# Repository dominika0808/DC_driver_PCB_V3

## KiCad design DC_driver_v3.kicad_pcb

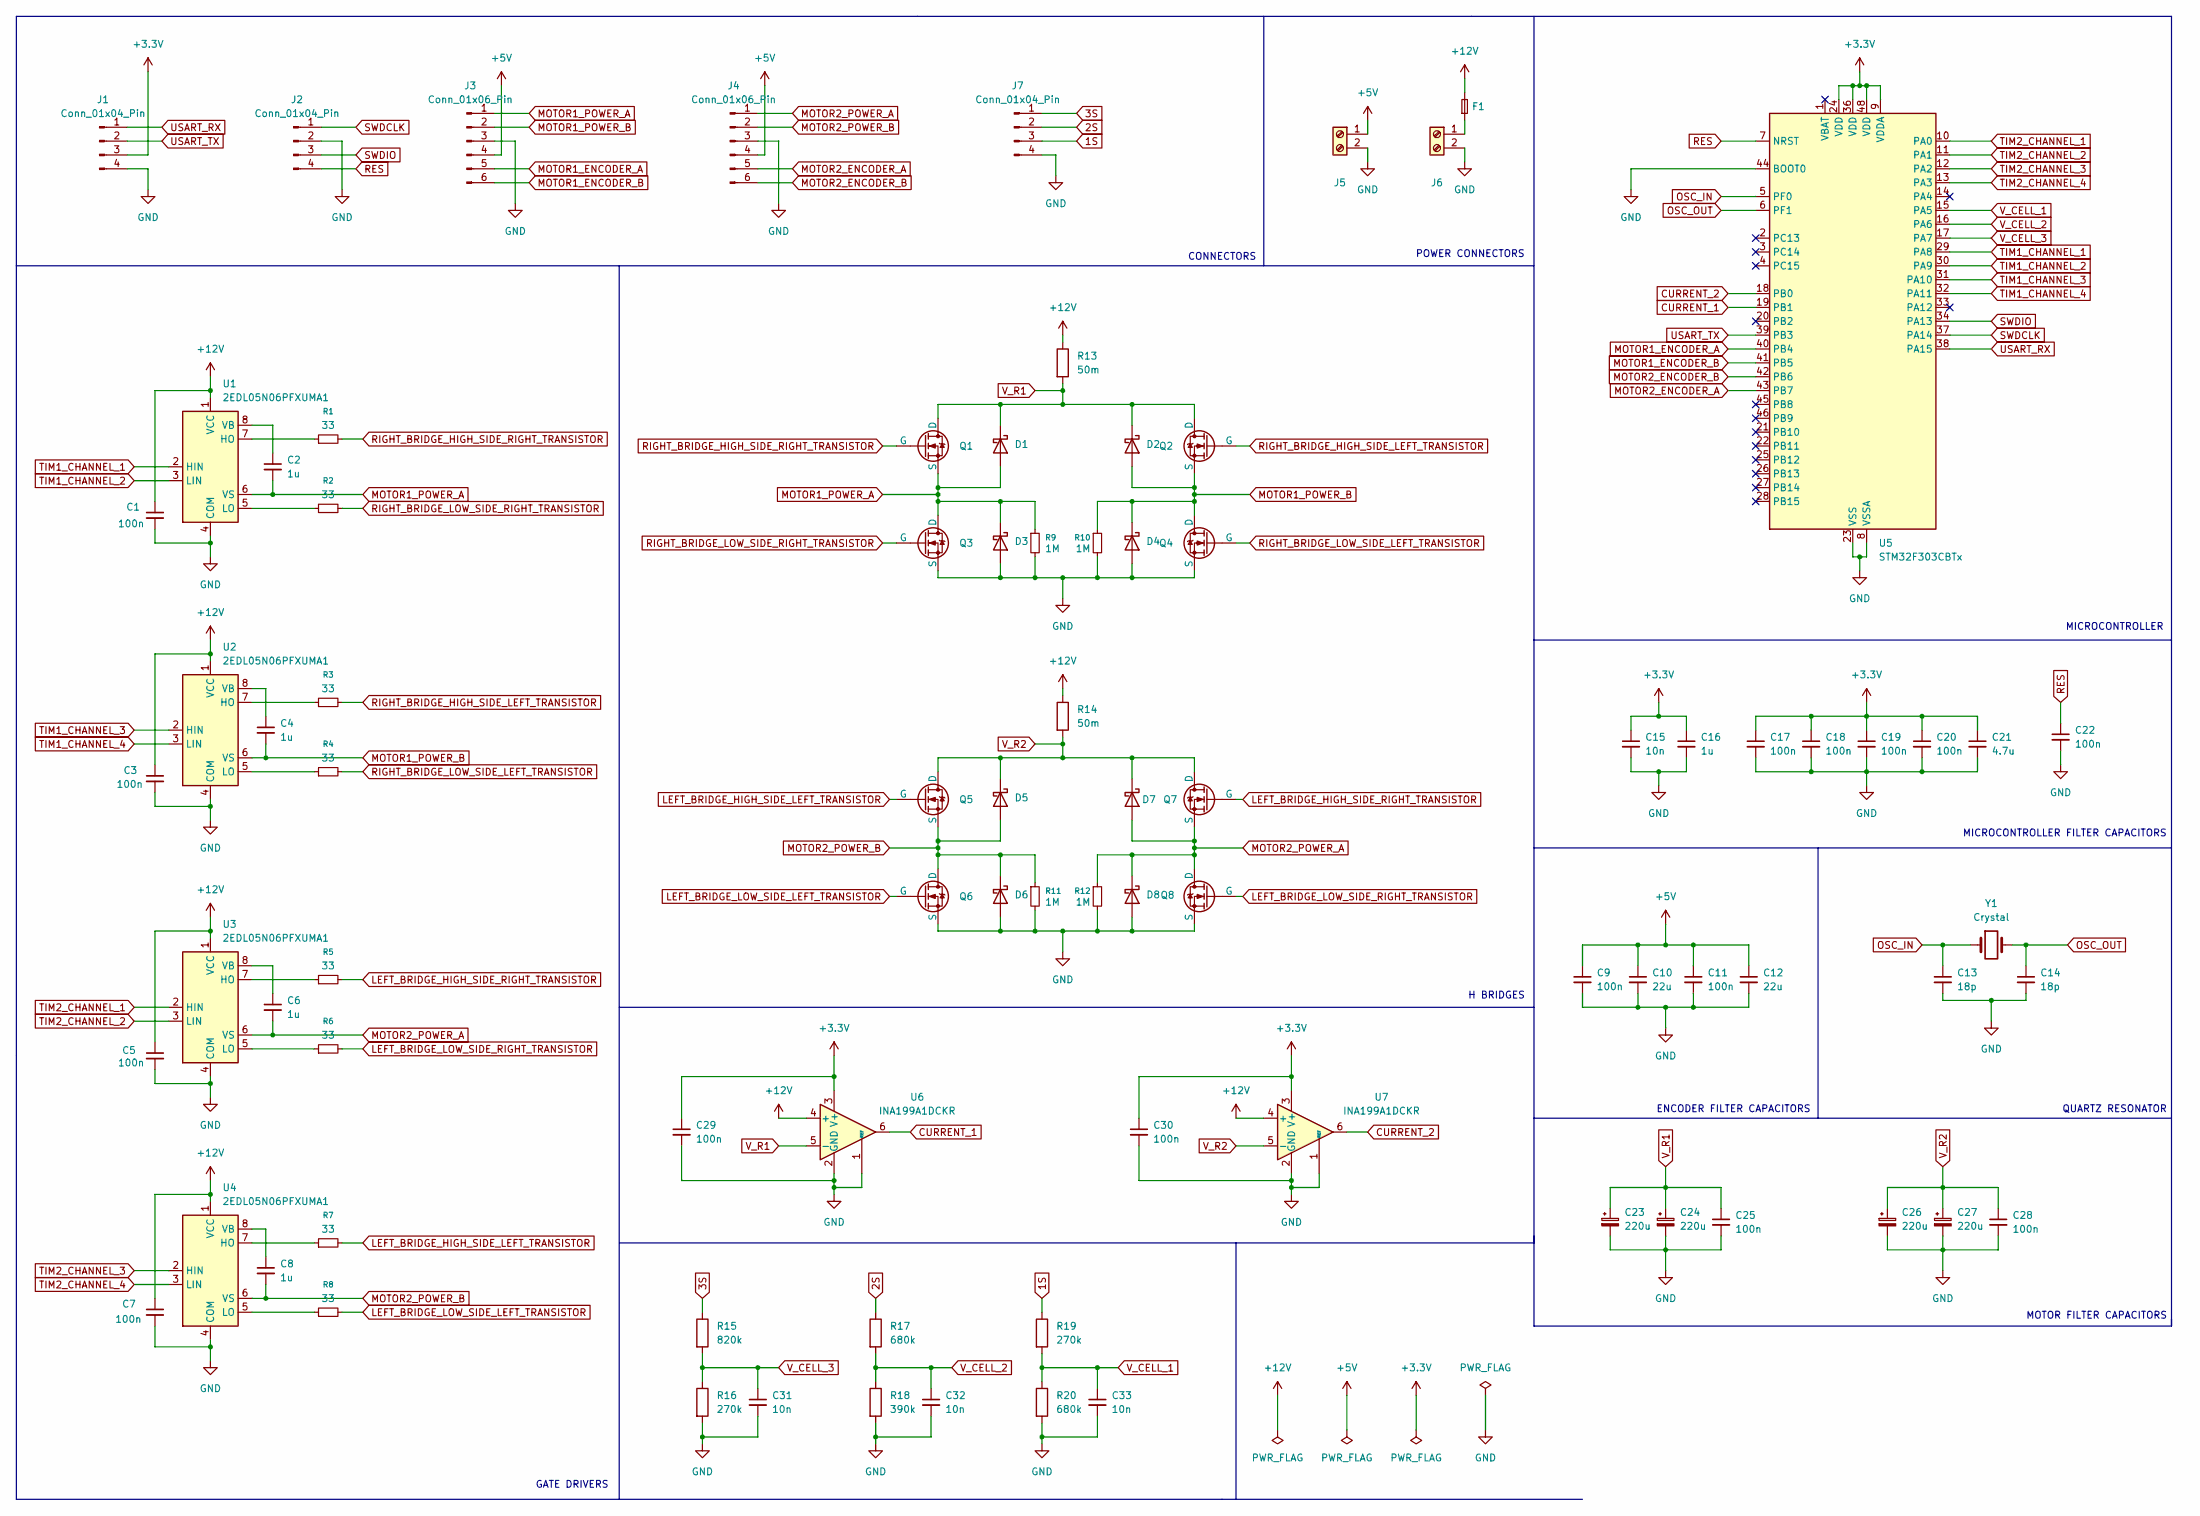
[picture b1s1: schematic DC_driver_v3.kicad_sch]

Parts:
C1, C3, C5, C7, C9, C11, C17, C18, C19, C20, C22, C29, C30: 100n; C_1206_3216Metric_Pad1.33x1.80mm_HandSolder
C2, C4, C6, C8, C16: 1u; C_1206_3216Metric_Pad1.33x1.80mm_HandSolder
C10, C12: 22u; CP_EIA-3528-21_Kemet-B_HandSolder
C13, C14: 18p; C_1206_3216Metric_Pad1.33x1.80mm_HandSolder
C15, C31, C32, C33: 10n; C_1206_3216Metric_Pad1.33x1.80mm_HandSolder
C21: 4.7u; C_1206_3216Metric_Pad1.33x1.80mm_HandSolder
C23, C24, C26, C27: 220u; CP_Radial_D8.0mm_P3.50mm
C25, C28: 100n; C_Rect_L7.0mm_W2.5mm_P5.00mm
D1, D2, D3, D4, D5, D6, D7, D8: 15MQ040NTR-SMC; D_SMA_Handsoldering
F1: Fuse_Small; Fuse_1206_3216Metric_Pad1.42x1.75mm_HandSolder
J1, J2: Conn_01x04_Pin; PinHeader_1x04_P2.54mm_Vertical
J3, J4: Conn_01x06_Pin; PinHeader_1x06_P2.54mm_Vertical
J5: Screw_Terminal_01x02; DG3813502P1300AH
J6: Screw_Terminal_01x02; DG3005002P1300AH
J7: Conn_01x04_Pin; PinSocket_1x04_P2.54mm_Vertical
Q1, Q2, Q3, Q4, Q5, Q6, Q7, Q8: AOD2544; TO-252-2
R1, R2, R3, R4, R5, R6, R7, R8: 33; R_1206_3216Metric_Pad1.30x1.75mm_HandSolder
R9, R10, R11, R12: 1M; R_1206_3216Metric_Pad1.30x1.75mm_HandSolder
R13, R14: 50m; R_1206_3216Metric_Pad1.30x1.75mm_HandSolder
R15: 820k; R_1206_3216Metric_Pad1.30x1.75mm_HandSolder
R16, R19: 270k; R_1206_3216Metric_Pad1.30x1.75mm_HandSolder
R17, R20: 680k; R_1206_3216Metric_Pad1.30x1.75mm_HandSolder
R18: 390k; R_1206_3216Metric_Pad1.30x1.75mm_HandSolder
U1, U2, U3, U4: 2EDL05N06PFXUMA1; SOIC127P600X175-8N
U5: STM32F303CBTx; LQFP-48_7x7mm_P0.5mm
U6, U7: INA199A1DCKR; SOT-363_SC-70-6
Y1: Crystal; Crystal_HC49-4H_Vertical

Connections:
1S: J7.3, R19.1
2S: J7.2, R17.1
3S: J7.1, R15.1
+3.3V: C15.1, C16.1, C17.1, C18.1, C19.1, C20.1, C21.1, C29.1, C30.1, J1.3, U5.9 (VDDA), U5.24 (VDD), U5.36 (VDD), U5.48 (VDD), U6.3 (V+), U7.3 (V+)
+5V: C9.1, C10.1, C11.1, C12.1, J3.4, J4.4, J5.1
+12V: C1.1, C3.1, C5.1, C7.1, F1.2, R13.1, R14.1, U1.1 (VCC), U2.1 (VCC), U3.1 (VCC), U4.1 (VCC), U6.4 (+), U7.4 (+)
CURRENT_1: U5.19 (PB1), U6.6
CURRENT_2: U5.18 (PB0), U7.6
GND: C1.2, C3.2, C5.2, C7.2, C9.2, C10.2, C11.2, C12.2, C13.2, C14.2, C15.2, C16.2, C17.2, C18.2, C19.2, C20.2, C21.2, C22.2, C23.2, C24.2, C25.2, C26.2, C27.2, C28.2, C29.2, C30.2, C31.2, C32.2, C33.2, D3.2 (A), D4.2 (A), D6.2 (A), D8.2 (A), J1.4, J2.2, J3.3, J4.3, J5.2, J6.2, J7.4, Q3.3 (S), Q4.3 (S), Q6.3 (S), Q8.3 (S), R9.2, R10.2, R11.2, R12.2, R16.2, R18.2, R20.2, U1.4 (COM), U2.4 (COM), U3.4 (COM), U4.4 (COM), U5.8 (VSSA), U5.23 (VSS), U5.35 (VSS), U5.44 (BOOT0), U5.47 (VSS), U6.1 (REF), U6.2 (GND), U7.1 (REF), U7.2 (GND)
LEFT_BRIDGE_HIGH_SIDE_LEFT_TRANSISTOR: Q5.1 (G), R7.2
LEFT_BRIDGE_HIGH_SIDE_RIGHT_TRANSISTOR: Q7.1 (G), R5.2
LEFT_BRIDGE_LOW_SIDE_LEFT_TRANSISTOR: Q6.1 (G), R8.2
LEFT_BRIDGE_LOW_SIDE_RIGHT_TRANSISTOR: Q8.1 (G), R6.2
MOTOR1_ENCODER_A: J3.5, U5.40 (PB4)
MOTOR1_ENCODER_B: J3.6, U5.41 (PB5)
MOTOR1_POWER_A: C2.2, D1.2 (A), D3.1 (K), J3.1, Q1.3 (S), Q3.2 (D), R9.1, U1.6 (VS)
MOTOR1_POWER_B: C4.2, D2.2 (A), D4.1 (K), J3.2, Q2.3 (S), Q4.2 (D), R10.1, U2.6 (VS)
MOTOR2_ENCODER_A: J4.5, U5.43 (PB7)
MOTOR2_ENCODER_B: J4.6, U5.42 (PB6)
MOTOR2_POWER_A: C6.2, D7.2 (A), D8.1 (K), J4.1, Q7.3 (S), Q8.2 (D), R12.1, U3.6 (VS)
MOTOR2_POWER_B: C8.2, D5.2 (A), D6.1 (K), J4.2, Q5.3 (S), Q6.2 (D), R11.1, U4.6 (VS)
unnamed: F1.1, J6.1
unnamed: R1.1, U1.7 (HO)
unnamed: R2.1, U1.5 (LO)
unnamed: C2.1, U1.8 (VB)
unnamed: R3.1, U2.7 (HO)
unnamed: R4.1, U2.5 (LO)
unnamed: C4.1, U2.8 (VB)
unnamed: R5.1, U3.7 (HO)
unnamed: R6.1, U3.5 (LO)
unnamed: C6.1, U3.8 (VB)
unnamed: R7.1, U4.7 (HO)
unnamed: R8.1, U4.5 (LO)
unnamed: C8.1, U4.8 (VB)
OSC_IN: C13.1, U5.5 (PF0), Y1.1
OSC_OUT: C14.1, U5.6 (PF1), Y1.2
RES: C22.1, J2.4, U5.7 (NRST)
RIGHT_BRIDGE_HIGH_SIDE_LEFT_TRANSISTOR: Q2.1 (G), R3.2
RIGHT_BRIDGE_HIGH_SIDE_RIGHT_TRANSISTOR: Q1.1 (G), R1.2
RIGHT_BRIDGE_LOW_SIDE_LEFT_TRANSISTOR: Q4.1 (G), R4.2
RIGHT_BRIDGE_LOW_SIDE_RIGHT_TRANSISTOR: Q3.1 (G), R2.2
SWDCLK: J2.1, U5.37 (PA14)
SWDIO: J2.3, U5.34 (PA13)
TIM1_CHANNEL_1: U1.2 (HIN), U5.29 (PA8)
TIM1_CHANNEL_2: U1.3 (LIN), U5.30 (PA9)
TIM1_CHANNEL_3: U2.2 (HIN), U5.31 (PA10)
TIM1_CHANNEL_4: U2.3 (LIN), U5.32 (PA11)
TIM2_CHANNEL_1: U3.2 (HIN), U5.10 (PA0)
TIM2_CHANNEL_2: U3.3 (LIN), U5.11 (PA1)
TIM2_CHANNEL_3: U4.2 (HIN), U5.12 (PA2)
TIM2_CHANNEL_4: U4.3 (LIN), U5.13 (PA3)
USART_RX: J1.1, U5.38 (PA15)
USART_TX: J1.2, U5.39 (PB3)
V_CELL_1: C33.1, R19.2, R20.1, U5.15 (PA5)
V_CELL_2: C32.1, R17.2, R18.1, U5.16 (PA6)
V_CELL_3: C31.1, R15.2, R16.1, U5.17 (PA7)
V_R1: C23.1, C24.1, C25.1, D1.1 (K), D2.1 (K), Q1.2 (D), Q2.2 (D), R13.2, U6.5 (-)
V_R2: C26.1, C27.1, C28.1, D5.1 (K), D7.1 (K), Q5.2 (D), Q7.2 (D), R14.2, U7.5 (-)

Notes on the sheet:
MICROCONTROLLER
POWER CONNECTORS
MOTOR FILTER CAPACITORS
QUARTZ RESONATOR
ENCODER FILTER CAPACITORS
H BRIDGES
GATE DRIVERS
CONNECTORS
MICROCONTROLLER FILTER CAPACITORS

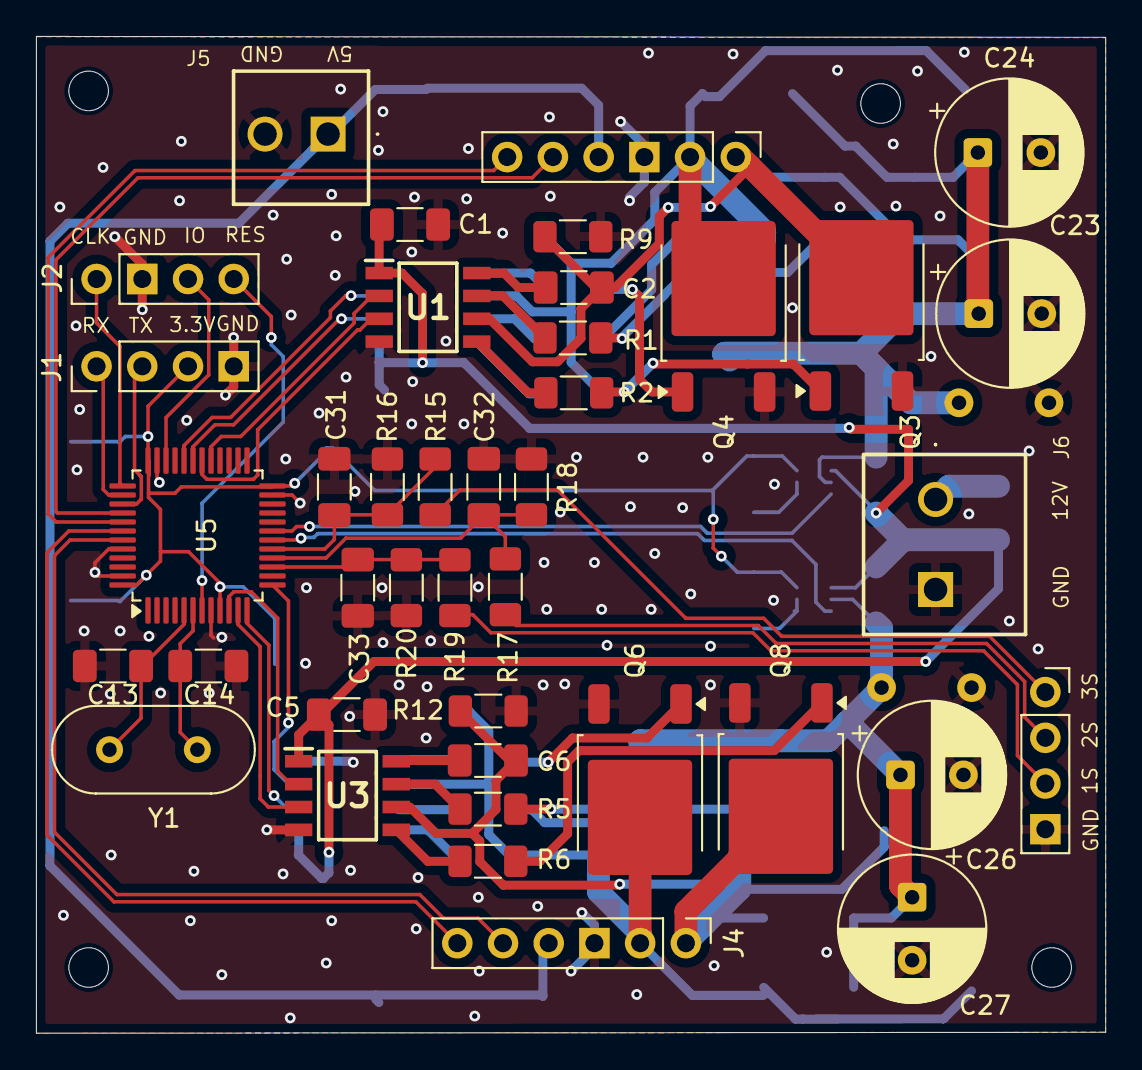
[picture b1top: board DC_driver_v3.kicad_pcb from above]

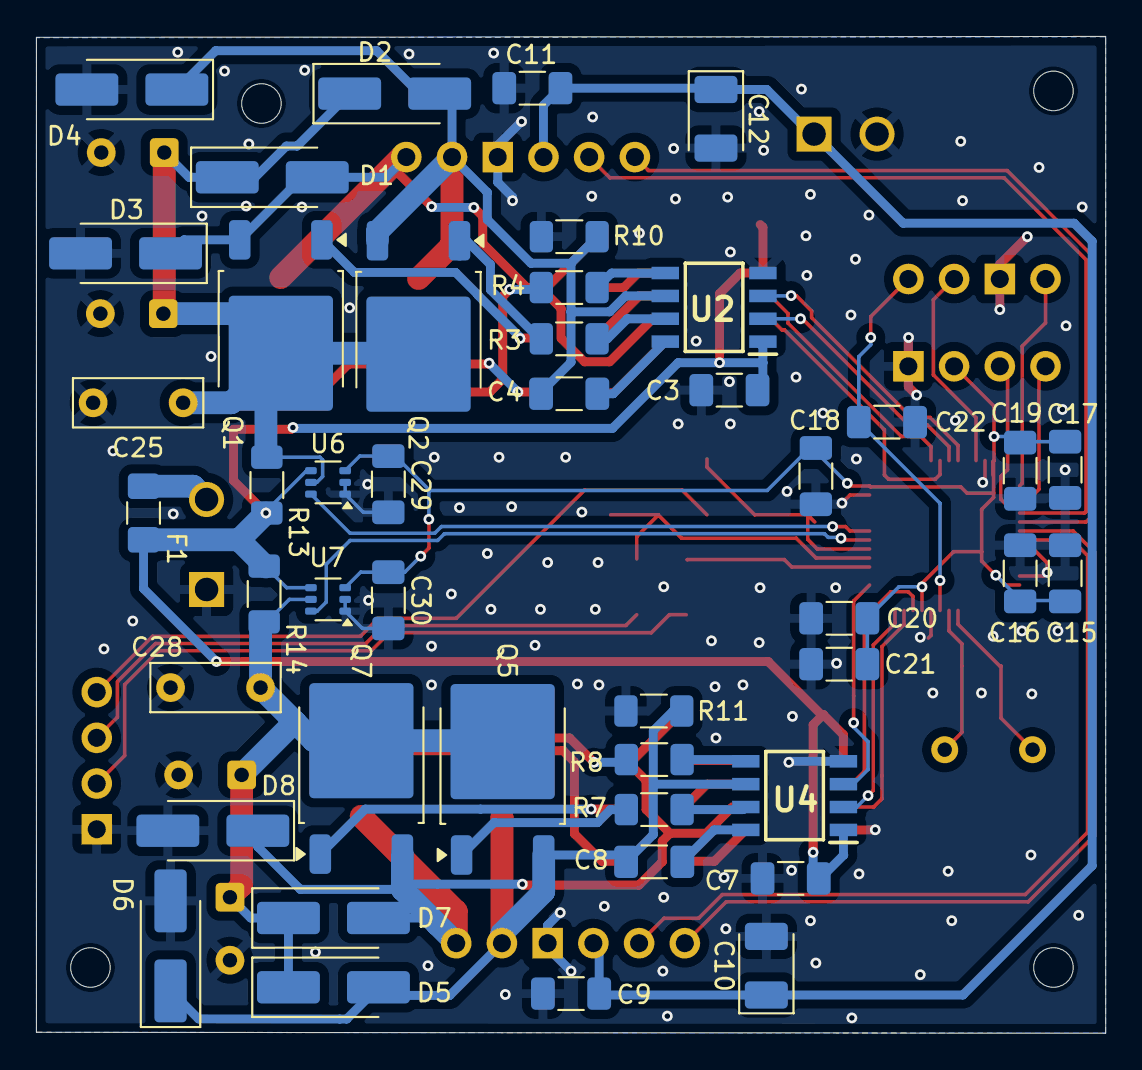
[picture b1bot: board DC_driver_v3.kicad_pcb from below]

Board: 2 copper layers, 59.4 x 55.4 mm, 85 parts (45 on the bottom side), 58 nets.

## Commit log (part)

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2026-06-02 first comit
